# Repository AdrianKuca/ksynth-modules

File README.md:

# ksynth-modules
Kicad PCB projects for my ongoing adventure in making an digital-analog synthesizer from ground up, including software (which gonna be in separate repos). 

The first board is FX0, universal board which can hold line in/out and cv in/out. 
Doesn't use a microprocessor by itself but instead uses whole modules: raspbbery pi Pico, seeduino Xiao or arduino pro micro (only one should be soldered at once).

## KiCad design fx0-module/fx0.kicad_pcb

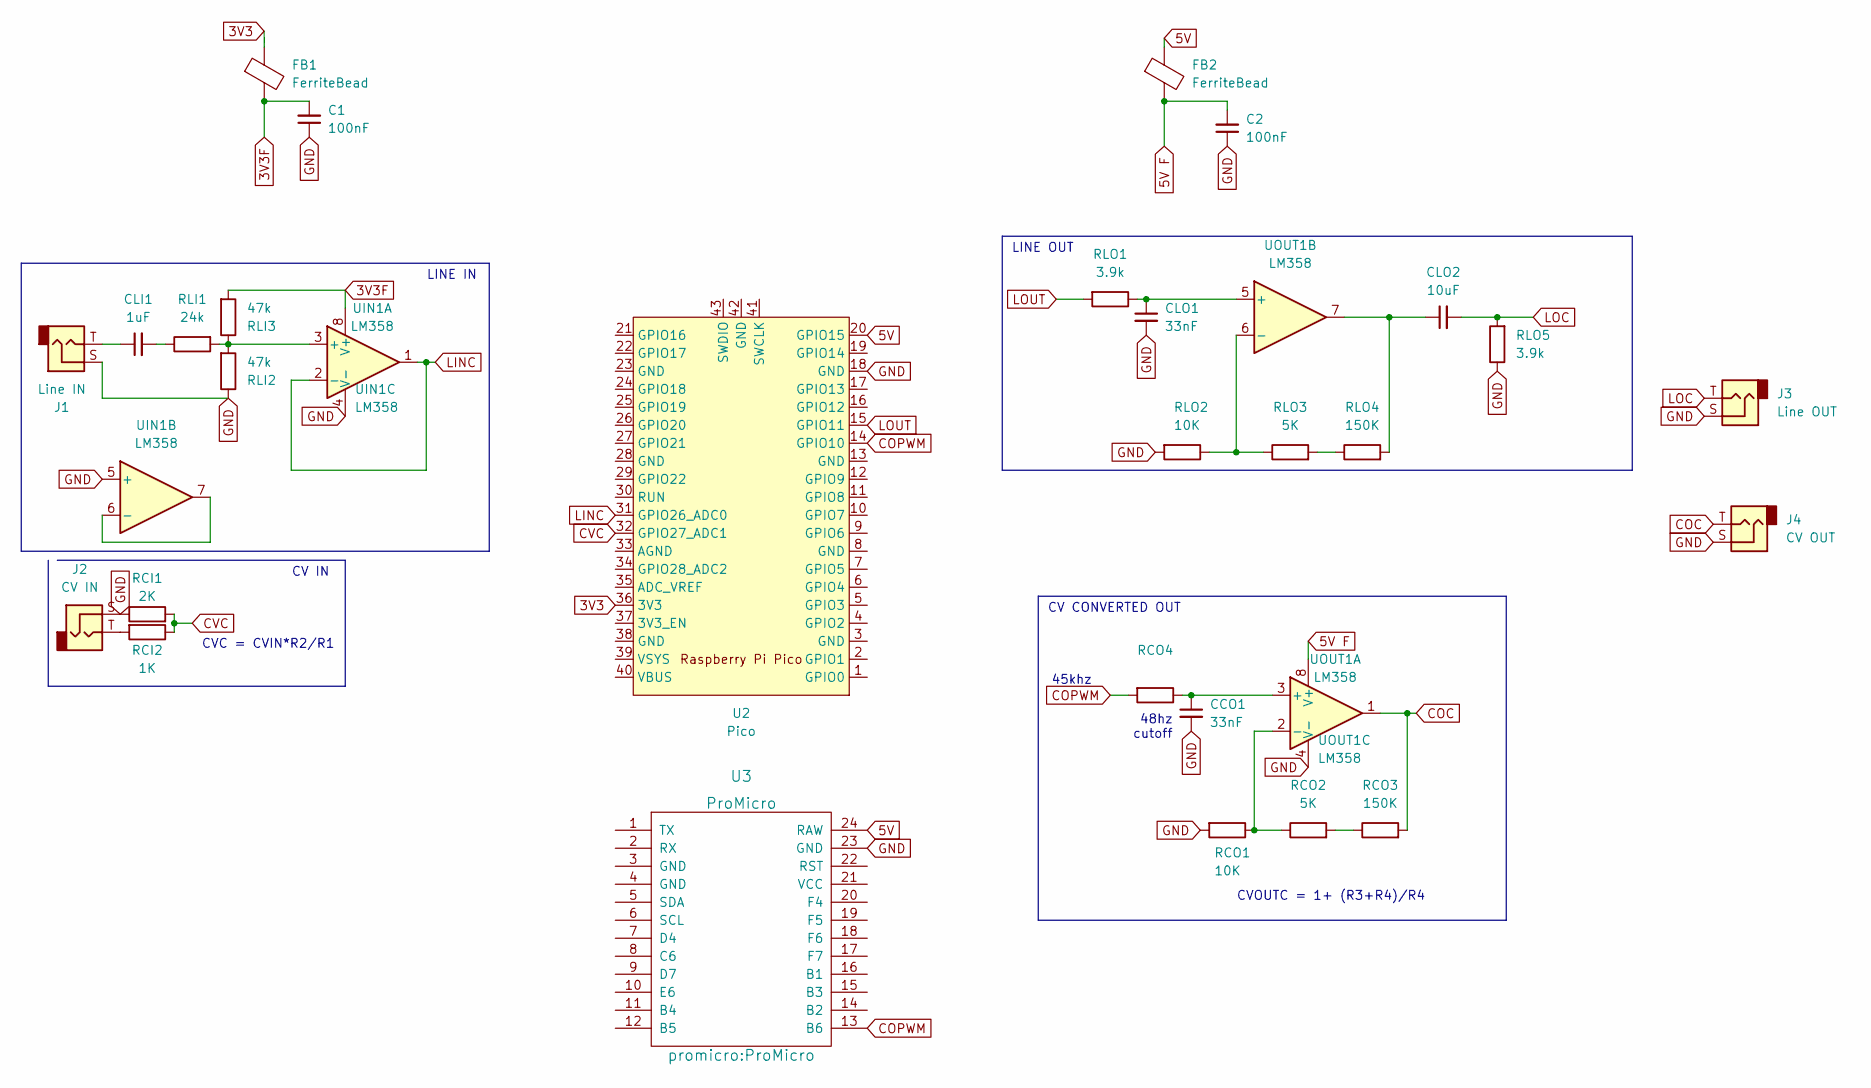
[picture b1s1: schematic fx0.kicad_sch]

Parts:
C1, C2: 100nF; C_0805_2012Metric_Pad1.18x1.45mm_HandSolder
CCO1: 33nF; C_0805_2012Metric_Pad1.18x1.45mm_HandSolder
CLI1: 1uF; C_0805_2012Metric_Pad1.18x1.45mm_HandSolder
CLO1: 33nF; C_0805_2012Metric_Pad1.18x1.45mm_HandSolder
CLO2: 10uF; C_0805_2012Metric_Pad1.18x1.45mm_HandSolder
FB1, FB2: FerriteBead; R_0805_2012Metric_Pad1.20x1.40mm_HandSolder
J1: Line IN; SolderWirePad_2x01_SMD_1x2mm
J2: CV IN; SolderWirePad_2x01_SMD_1x2mm
J3: Line OUT; SolderWirePad_2x01_SMD_1x2mm
J4: CV OUT; SolderWirePad_2x01_SMD_1x2mm
RCI1: 2K; R_0805_2012Metric_Pad1.20x1.40mm_HandSolder
RCI2: 1K; R_0805_2012Metric_Pad1.20x1.40mm_HandSolder
RCO1: 10K; R_0805_2012Metric_Pad1.20x1.40mm_HandSolder
RCO2: 5K; R_0805_2012Metric_Pad1.20x1.40mm_HandSolder
RCO3: 150K; R_0805_2012Metric_Pad1.20x1.40mm_HandSolder
RCO4: R_0805_2012Metric_Pad1.20x1.40mm_HandSolder
RLI1: 24k; R_0805_2012Metric_Pad1.20x1.40mm_HandSolder
RLI2, RLI3: 47k; R_0805_2012Metric_Pad1.20x1.40mm_HandSolder
RLO1, RLO5: 3.9k; R_0805_2012Metric_Pad1.20x1.40mm_HandSolder
RLO2: 10K; R_0805_2012Metric_Pad1.20x1.40mm_HandSolder
RLO3: 5K; R_0805_2012Metric_Pad1.20x1.40mm_HandSolder
RLO4: 150K; R_0805_2012Metric_Pad1.20x1.40mm_HandSolder
U2: Pico; RPi_Pico_SMD_TH
U3: ProMicro
UIN1: LM358; SOP-8_3.9x4.9mm_P1.27mm
UOUT1: LM358; SOP-8_3.9x4.9mm_P1.27mm

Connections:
3V3: FB1.1, U2.36 (3V3)
3V3F: C1.2, FB1.2, RLI3.2, UIN1.8 (V+)
5V: FB2.1, U2.20 (GPIO15), U3.24 (RAW)
5V F: C2.2, FB2.2, UOUT1.8 (V+)
COC: J4.T, RCO3.2, UOUT1.1
COPWM: RCO4.2, U2.14 (GPIO10), U3.13 (B6)
CVC: RCI1.2, RCI2.1, U2.32 (GPIO27_ADC1)
GND: C1.1, C2.1, CCO1.2, CLO1.2, J1.S, J2.S, J3.S, J4.S, RCI1.1, RCO1.2, RLI2.1, RLO2.2, RLO5.1, U2.18 (GND), U3.23 (GND), UIN1.4 (V-), UIN1.5 (+), UOUT1.4 (V-)
LINC: U2.31 (GPIO26_ADC0), UIN1.1, UIN1.2 (-)
LOC: CLO2.2, J3.T, RLO5.2
LOUT: RLO1.2, U2.15 (GPIO11)
unnamed: CCO1.1, RCO4.1, UOUT1.3 (+)
unnamed: CLI1.1, J1.T
unnamed: CLI1.2, RLI1.1
unnamed: CLO1.1, RLO1.1, UOUT1.5 (+)
unnamed: CLO2.1, RLO4.2, UOUT1.7
unnamed: J2.T, RCI2.2
unnamed: RCO1.1, RCO2.1, UOUT1.2 (-)
unnamed: RCO2.2, RCO3.1
unnamed: RLI1.2, RLI2.2, RLI3.1, UIN1.3 (+)
unnamed: RLO2.1, RLO3.1, UOUT1.6 (-)
unnamed: RLO3.2, RLO4.1
unnamed: UIN1.6 (-), UIN1.7

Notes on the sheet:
45khz
CVC = CVIN*R2/R1
LINE IN
CV CONVERTED OUT
CVOUTC = 1+ (R3+R4)/R4
CV IN
LINE OUT
48hz cutoff

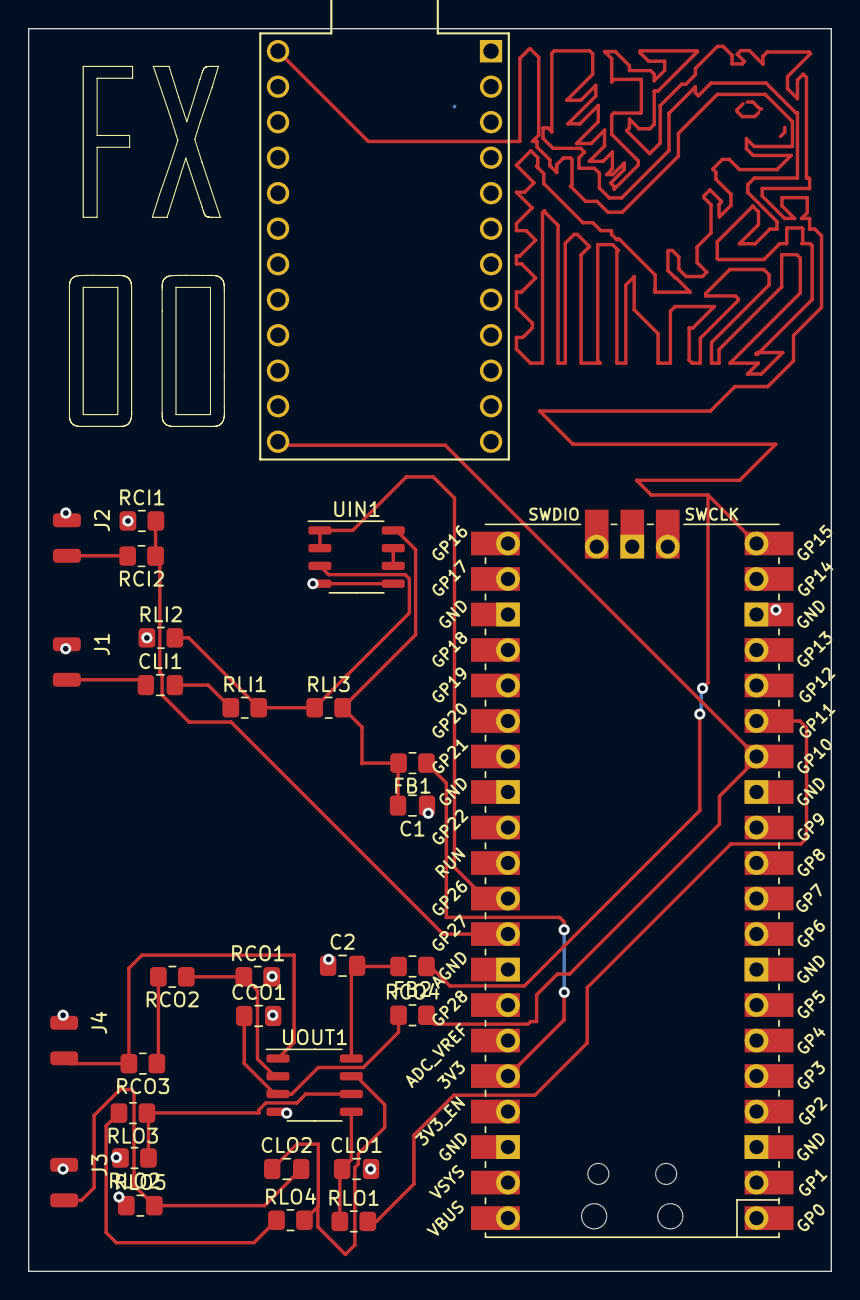
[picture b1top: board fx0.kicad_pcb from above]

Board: 2 copper layers, 57.4 x 88.9 mm, 30 parts (1 on the bottom side), 23 nets.

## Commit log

2022-04-26 Add empty fx0 project
2022-04-26 Add gitignore
2022-04-26 Rename dir and draft project
2022-04-26 Add another library
2022-04-26 Add pcb draft
2022-05-02 Finish up the fx0 board project
2022-05-02 Add fx00 name on board
2022-05-07 Add ground plane and decouple opamps
2022-05-09 Fix buzzing voltage on line in
2022-05-09 Fix flying silk layer
2022-10-10 Redraw pcb with proper op amp legs and no seeduino
2022-11-16 Change value for rc filter
2022-11-24 Add analog one module
